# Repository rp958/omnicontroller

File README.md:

# OmniController

## Description

*OmniController* is an Open Hardware /  Open Source, all-in-one controller.

It was conceived with retrogaming solutions (such as emulators or FPGA) in mind but can accommodate to modern gaming as well. Its main goal is to cover original button layouts of most of the popular console controllers without having to remap buttons or use different controllers when playing games from different consoles libraries.

It uses the [**GP2040-CE**](https://gp2040-ce.info/) firmware which is well known for its [compatibility](https://gp2040-ce.info/usage#input-modes) with most modern and retro platforms as well as its [very low latency](https://gp2040-ce.info/#performance).

## Default keymap

Please note that the double L3 and R3 buttons (the ones on the joysticks and the face buttons ones) are wired in hardware. That means that if you chose, for exemple, to remap L3 to a different button, both L3s will be remapped to that button. This is due to the fact that all GPIOs available in the firmware/microcontroller are already in use. It is unlikely that you will need to use both joysticks and 6 faces buttons at the same time.

## Getting Started

### Prerequisites

Software:
- Firmware: [**GP2040-CE**](https://gp2040-ce.info/)
- (optional for modifying the PCB): [**KiCAD**](https://www.kicad.org/)
- (optional for modifying the case and buttons): [**FreeCAD**](https://www.freecad.org/)

Hardware:
- 4x M2x4x3.2 threaded inserts
- 4x M2x12 screws
- a soldering iron (to melt the inserts into the case, no actual soldering required)
- super glue
- USB-C cable
- a computer for installing the firmware

### Making the PCB

Download and extract the latest [*OmniController* release](https://github.com/rp958/omnicontroller/releases) file.

All the necessary files for PCB fabrication are located in *release/pcb/*.

Bill of materials:

| Item# | Designation                                                                                 | Manufacturer      | Part Number            | Package               | Value              | Quantity |
|-------|---------------------------------------------------------------------------------------------|-------------------|------------------------|-----------------------|--------------------|----------|
| 1     | UP1, DOWN1, LEFT1, RIGHT1, Credit1, Menu1, SEL1, START1, A1, B1, bC1, X1, Y2, Z1, BOOT_SEL1 | Omron Electronics | B3FS-1000P             |                       |                    | 15       |
| 2     | bR1, bR2, bL1, bL2                                                                          | Omron Electronics | B3F-3100               |                       |                    | 4        |
| 3     | C1, C2                                                                                      |                   |                        | 0805 (2012 Metric)    | 10u capacitor      | 2        |
| 4     | C10, C11                                                                                    |                   |                        | 0805 (2012 Metric)    | 1u capacitor       | 2        |
| 5     | C12, C13, C14, C3, C4, C5, C6, C7, C8, C9                                                   |                   |                        | 0805 (2012 Metric)    | 100n capacitor     | 10       |
| 6     | C15, C16                                                                                    |                   |                        | 0805 (2012 Metric)    | 15p capacitor      | 2        |
| 7     | LeftStick1, RightStick1                                                                     | Alps              | RKJXV122400R           | (THT)                 |                    | 2        |      
| 8     | J1                                                                                          | G-Switch          | GT-USB-7010ASV         |                       |                    | 1        |
| 9     | R1, R2                                                                                      |                   |                        | 0805 (2012 Metric)    | 27.4 ohms resistor | 2        |
| 10    | R3, R4                                                                                      |                   |                        | 0805 (2012 Metric)    | 1k resistor        | 2        |
| 11    | U1                                                                                          | Raspberry Pi      | RP2040                 | QFN-56 7×7mm          |                    | 1        |
| 12    | U2                                                                                          | Onsemi            | NCP1117ST33T3G         | SOT-223-3_TabPin2     |                    | 1        |
| 13    | U3                                                                                          | Winbond           | W25Q128JVSIM           | SOIC 208-mil          |                    | 1        |
| 14    | Y1                                                                                          | Abracon           | ABM8-272-T3            | Crystal SMD 3225 4Pin |                    | 1        |
| 15    | (Optionnal) J2                                                                              | GCT               | USB1046-GF-0190-L-B-B  | USB_A_Receptacle      |                    | 1        |

NOTE: J2 is only necessary for *Host USB* authentication mode. If not needed, can be left unpopulated.

NOTE: J3 is for development of and does not require populating.

### 3D Printing the case and buttons

You will need to print the following parts (all contained in *release/case/*).

Buttons:
- [ ] 1x dpad_bottom
- [ ] 1x dpad_top
- [ ] 2x joystick
- [ ] 2x button_select_start
- [ ] 2x button_cred_home
- [ ] 4x button_L_R
- [ ] 6x button_face 

Case:
- [ ] 1x case_back
- [ ] 1x case_front
- [ ] 1x middle_frame

For better printing results, it is recommended the following parts be sliced at an angle of 45 degrees and with supports:
- the joysticks
- case_top
- case_bottom

All the other parts should be printed flat and do not require any support.

Please note that depending on the quality and precision of your print, you might have to sand some parts.

### Assembling

1. Take the 2 parts of the D-Pad and glue them together back to back, making sure the two holes are aligned. 
2. Take the case front, melt the threaded inserts into the 4 holes using the soldering iron. 
3. Place all the face controls as well as L1 and R1 in their respective place. Make sure the rectangular holes in the back of the joysticks are placed horizontally. 
4. Place the PCB aligning the holes with the M2 inserts. Make sure the joystick axes go into the rectangular holes. 
5. Insert the middle frame. 
6. Place the L2 and R2 buttons. 
7. Close the controller using the back part, then screw it using the 4 M2 screws. Screw them firmly but not too tight. 
8. You're done!

### Flashing the firmware

1. Download the latest version of **GP2040-CE** from the project's [download page](https://gp2040-ce.info/downloads). You must use the link for the **Raspberry Pi Pico** microcontroller.
2. Unplug your controller.
3. Use a pin or an unfolded paperclip to press the reset button at the back of the controller. 
4. While pressing the reset button, plug the controller to your computer. Your computer should detect your controller as a mass storage device.
5. Copy the *.uf2* firmware file to the controller memory.
6. Once the file copy is finished, the controller should restart and be detected as an XInput (XBox360) controller by default.

Please refer to the [**GP2040-CE** installation documentation](https://gp2040-ce.info/installation) for more details.

### Recommended configuration

1. Unplug your controller.
2. Download the default [*omnicontroller_default.gp2040*](conf/omnicontroller_default.gp2040) configuration file on your computer.
3. Press and hold the S2 button. While still holding S2, plug the controller to your computer. Your computer should detect your controller as a network adapter.
4. Open the following URL in your Web Browser: [http://192.168.7.1](http://192.168.7.1). This should bring you to the *Web Configurator* interface.
5. Go to *Configuration* > *Data Backup and Restoration*.
6. Click on *Load* and select the *omnicontroller_default.gp2040* file you downloaded at step 2.
7. Click the *REBOOT* button, then *Controller*.

Please refer to the [**GP2040-CE** *Web Configurator* documentation](https://gp2040-ce.info/web-configurator/) for more details.

### Usage
 
Please refer to the [**GP2040-CE** usage documentation](https://gp2040-ce.info/usage)

### Troubleshooting

In case of problems, you can use **Hardware Tester's** [gamepad controller](https://hardwaretester.com/gamepad) in order to make sure you controller is detected correctly and that all buttons are functioning.

## Roadmap

- Several new features are considered, for instance adding an OLED screen, rumble, colord LEDs. Please join the discord via the project's [Patreon](https://www.patreon.com/omnicontroller) for discussing new features and/or new features prioritization.

## Known issues / Limitations

- At this stage, *Host USB* authentication mode for PS4/PS5 is implemented but has not been tester. Please read [*Additionnal PS4 settings*](https://gp2040-ce.info/web-configurator/menu-pages/settings/#additional-ps4-settings) from **GP2040-CE** *Settings* documentation. Any feedback is appreciated.

## License

Distributed under CERN-OHL-S version 2 or later. See [licence text](https://ohwr.org/cern_ohl_s_v2.txt) for more information.

## Contact

Please [e-mail me](mailto:omnicontroller@proton.me) if you want to contribute, especially if you have experience in electronics engineering, CAD or manufacturing.

## Attributions

OmniController uses several KiCAD component footprints and models from the [SnapEDA library](https://www.snapeda.com/parts/).

## Acknowledgments

Many thanks go to the [**GP2040-CE**](https://gp2040-ce.info/) development team.

## Help

If you want to help funding this project, any contribution is greatly welcome. This can help me acquire some prototyping equipment and spend more time on the development. To do so, please use my:

- [  Patreon](https://www.patreon.com/omnicontroller) page.
- [  Ko-fi](https://ko-fi.com/omnicontroller) page.

Thank you.

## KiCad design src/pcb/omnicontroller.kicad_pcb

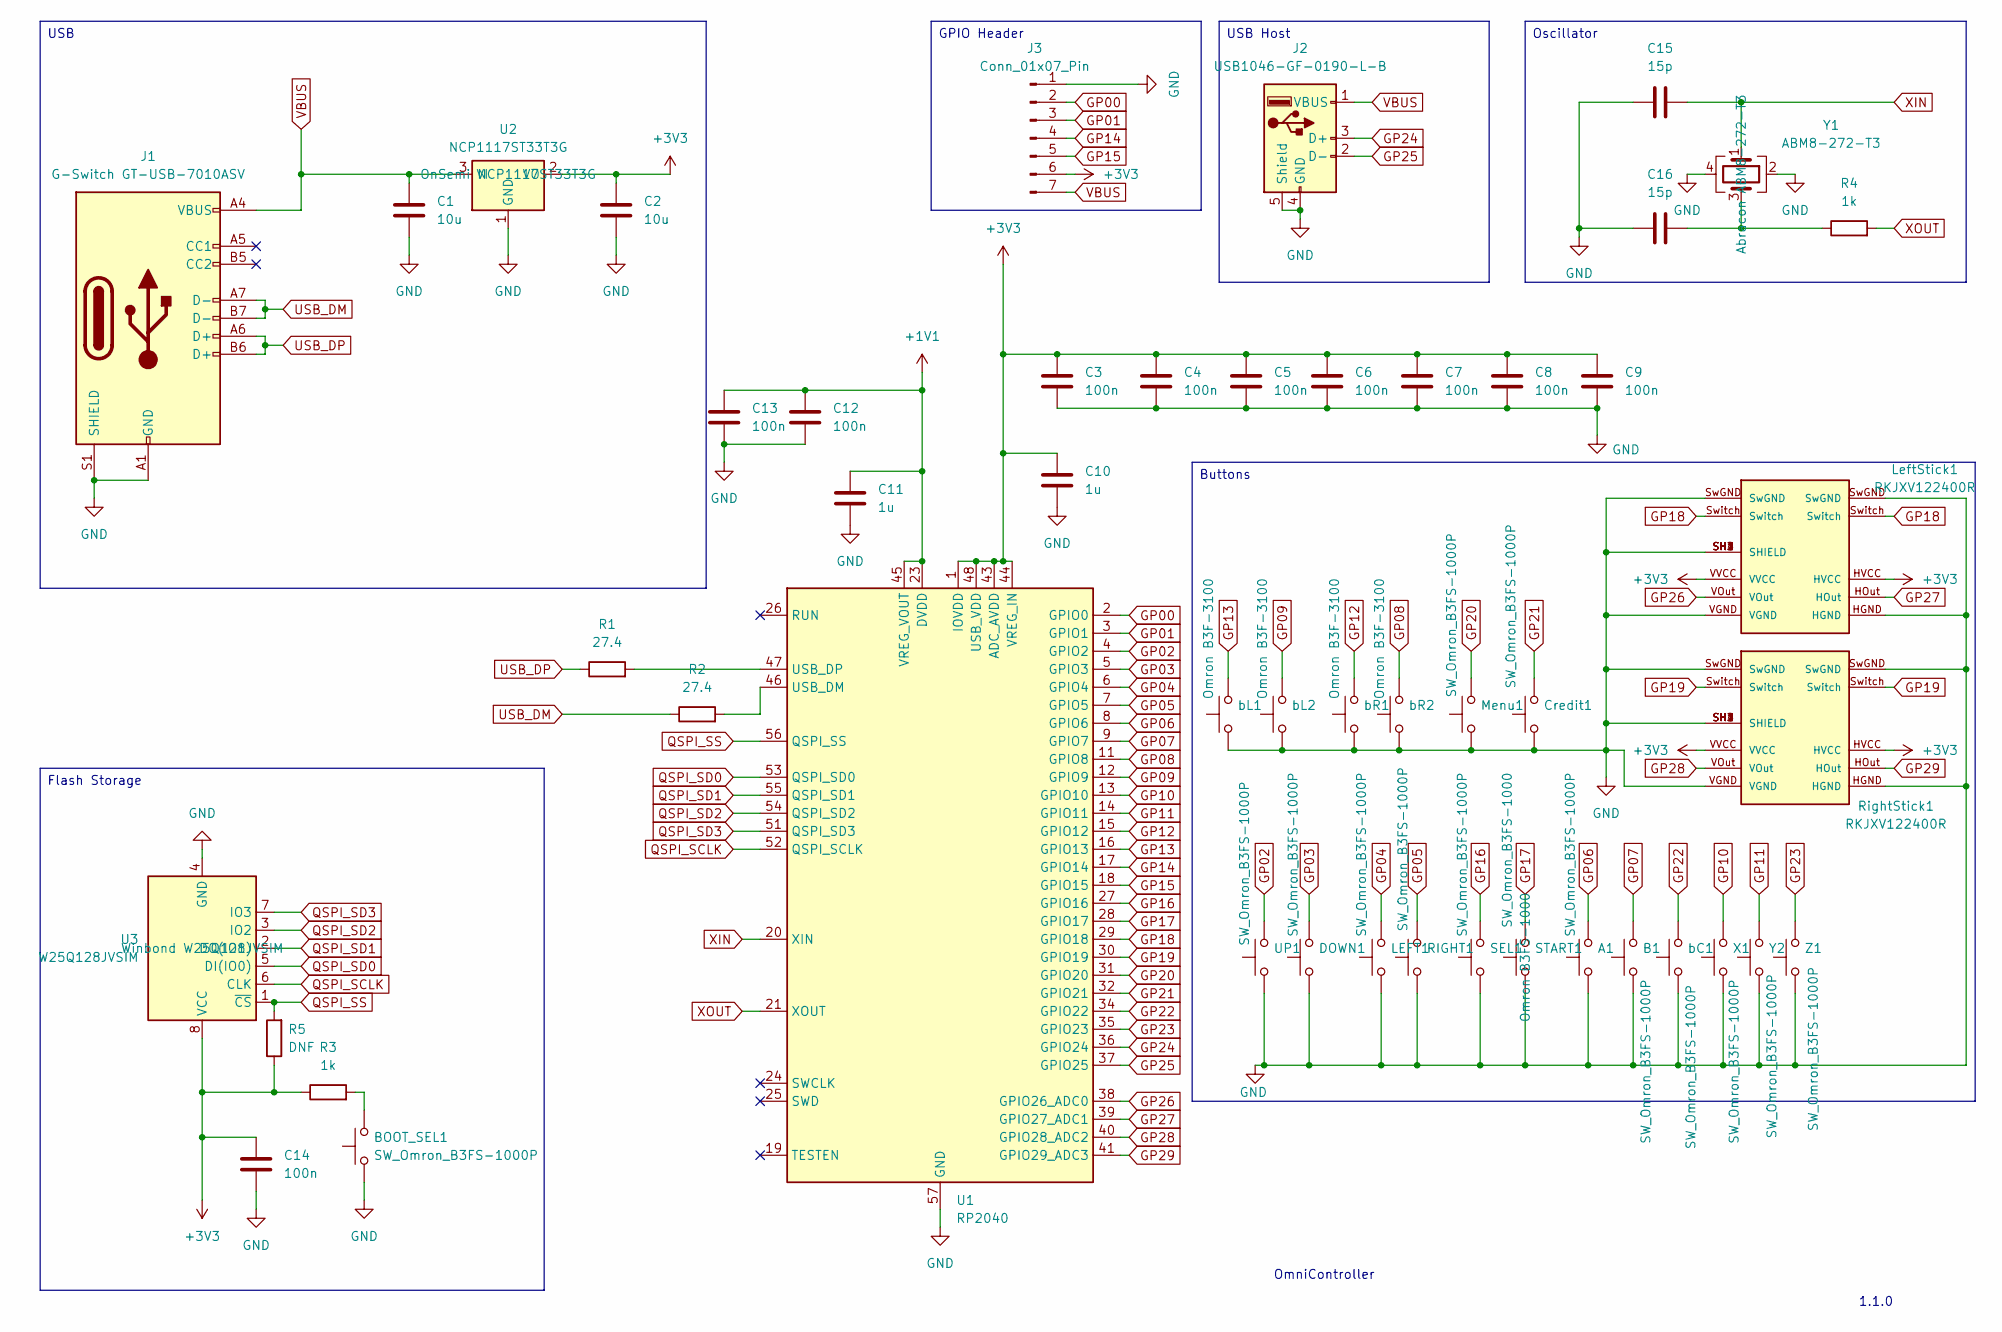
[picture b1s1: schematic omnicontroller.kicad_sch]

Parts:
A1: SW_Omron_B3FS-1000P; SW_SPST_Omron_B3FS-100xP
B1: SW_Omron_B3FS-1000P; SW_SPST_Omron_B3FS-100xP
BOOT_SEL1: SW_Omron_B3FS-1000P; SW_SPST_Omron_B3FS-100xP
C1, C2: 10u; C_0805_2012Metric
C3, C4, C5, C6, C7, C8, C9, C12, C13, C14: 100n; C_0805_2012Metric
C10, C11: 1u; C_0805_2012Metric
C15, C16: 15p; C_0805_2012Metric
Credit1: SW_Omron_B3FS-1000P; SW_SPST_Omron_B3FS-100xP
DOWN1: SW_Omron_B3FS-1000P; SW_SPST_Omron_B3FS-100xP
J1: G-Switch GT-USB-7010ASV; USB_C_Receptacle_G-Switch_GT-USB-7010ASV
J2: USB1046-GF-0190-L-B; USB_A_Receptacle_GCT_USB1046
J3: Conn_01x07_Pin; PinHeader_1x07_P2.54mm_Horizontal
LEFT1: SW_Omron_B3FS-1000P; SW_SPST_Omron_B3FS-100xP
LeftStick1: RKJXV122400R; SW_RKJXV122400R; PARTREV N/A
Menu1: SW_Omron_B3FS-1000P; SW_SPST_Omron_B3FS-100xP
R1, R2: 27.4; C_0805_2012Metric
R3, R4: 1k; C_0805_2012Metric
R5: DNF; C_0805_2012Metric
RIGHT1: SW_Omron_B3FS-1000P; SW_SPST_Omron_B3FS-100xP
RightStick1: RKJXV122400R; SW_RKJXV122400R; PARTREV N/A
SEL1: SW_Omron_B3FS-1000P; SW_SPST_Omron_B3FS-100xP
START1: SW_Omron_B3FS-1000; SW_SPST_Omron_B3FS-100xP
U1: RP2040; QFN-56-1EP_7x7mm_P0.4mm_EP3.2x3.2mm
U2: NCP1117ST33T3G; SOT-223-3_TabPin2
U3: W25Q128JVSIM; SOIC-8_5.3x5.3mm_P1.27mm
UP1: SW_Omron_B3FS-1000P; SW_SPST_Omron_B3FS-100xP
X1: SW_Omron_B3FS-1000P; SW_SPST_Omron_B3FS-100xP
Y1: ABM8-272-T3; Crystal_SMD_3225-4Pin_3.2x2.5mm
Y2: SW_Omron_B3FS-1000P; SW_SPST_Omron_B3FS-100xP
Z1: SW_Omron_B3FS-1000P; SW_SPST_Omron_B3FS-100xP
bC1: SW_Omron_B3FS-1000P; SW_SPST_Omron_B3FS-100xP
bL1, bL2: SW_B3F-3100
bR1, bR2: SW_B3F-3100

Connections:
+1V1: C11.1, C12.1, C13.1, U1.23 (DVDD), U1.45 (VREG_VOUT), U1.50 (DVDD)
GND: A1.1, B1.1, BOOT_SEL1.1, C1.2, C2.2, C3.2, C4.2, C5.2, C6.2, C7.2, C8.2, C9.2, C10.2, C11.2, C12.2, C13.2, C14.2, C15.1, C16.1, Credit1.1, DOWN1.1, J1.A1 (GND), J1.A12 (GND), J1.B1 (GND), J1.B12 (GND), J1.S1 (SHIELD), J2.4 (GND), J2.5 (Shield), J3.1, LEFT1.1, LeftStick1.HGND, LeftStick1.SH1 (SHIELD), LeftStick1.SH2 (SHIELD), LeftStick1.SH3 (SHIELD), LeftStick1.SH4 (SHIELD), LeftStick1.SwGND, LeftStick1.VGND, Menu1.1, RIGHT1.1, RightStick1.HGND, RightStick1.SH1 (SHIELD), RightStick1.SH2 (SHIELD), RightStick1.SH3 (SHIELD), RightStick1.SH4 (SHIELD), RightStick1.SwGND, RightStick1.VGND, SEL1.1, START1.1, U1.57 (GND), U2.1 (GND), U3.4 (GND), UP1.1, X1.1, Y1.2, Y1.4, Y2.1, Z1.1, bC1.1, bL1.1, bL2.1, bR1.1, bR2.1
GP00: J3.2, U1.2 (GPIO0)
GP01: J3.3, U1.3 (GPIO1)
GP02: U1.4 (GPIO2), UP1.2
GP03: DOWN1.2, U1.5 (GPIO3)
GP04: LEFT1.2, U1.6 (GPIO4)
GP05: RIGHT1.2, U1.7 (GPIO5)
GP06: A1.2, U1.8 (GPIO6)
GP07: B1.2, U1.9 (GPIO7)
GP08: U1.11 (GPIO8), bR2.2
GP09: U1.12 (GPIO9), bL2.2
GP10: U1.13 (GPIO10), X1.2
GP11: U1.14 (GPIO11), Y2.2
GP12: U1.15 (GPIO12), bR1.2
GP13: U1.16 (GPIO13), bL1.2
GP14: J3.4, U1.17 (GPIO14)
GP15: J3.5, U1.18 (GPIO15)
GP16: SEL1.2, U1.27 (GPIO16)
GP17: START1.2, U1.28 (GPIO17)
GP18: LeftStick1.Switch, U1.29 (GPIO18)
GP19: RightStick1.Switch, U1.30 (GPIO19)
GP20: Menu1.2, U1.31 (GPIO20)
GP21: Credit1.2, U1.32 (GPIO21)
GP22: U1.34 (GPIO22), bC1.2
GP23: U1.35 (GPIO23), Z1.2
GP24: J2.3 (D+), U1.36 (GPIO24)
GP25: J2.2 (D-), U1.37 (GPIO25)
GP26: LeftStick1.VOut, U1.38 (GPIO26_ADC0)
GP27: LeftStick1.HOut, U1.39 (GPIO27_ADC1)
GP28: RightStick1.VOut, U1.40 (GPIO28_ADC2)
GP29: RightStick1.HOut, U1.41 (GPIO29_ADC3)
unnamed: BOOT_SEL1.2, R3.2
unnamed: C16.2, R4.1, Y1.3
unnamed: R2.2, U1.46 (USB_DM)
unnamed: R1.2, U1.47 (USB_DP)
QSPI_SCLK: U1.52 (QSPI_SCLK), U3.6 (CLK)
QSPI_SD0: U1.53 (QSPI_SD0), U3.5 (DI(IO0))
QSPI_SD1: U1.55 (QSPI_SD1), U3.2 (DO(IO1))
QSPI_SD2: U1.54 (QSPI_SD2), U3.3 (IO2)
QSPI_SD3: U1.51 (QSPI_SD3), U3.7 (IO3)
USB_DM: J1.A7 (D-), J1.B7 (D-), R2.1
USB_DP: J1.A6 (D+), J1.B6 (D+), R1.1
VBUS: C1.1, J1.A4 (VBUS), J1.A9 (VBUS), J1.B4 (VBUS), J1.B9 (VBUS), J2.1 (VBUS), J3.7, U2.3 (VI)
XIN: C15.2, U1.20 (XIN), Y1.1
XOUT: R4.2, U1.21 (XOUT)

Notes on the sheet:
1.1.0
OmniController
Flash Storage
Buttons
USB
USB Host
Oscillator
GPIO Header

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
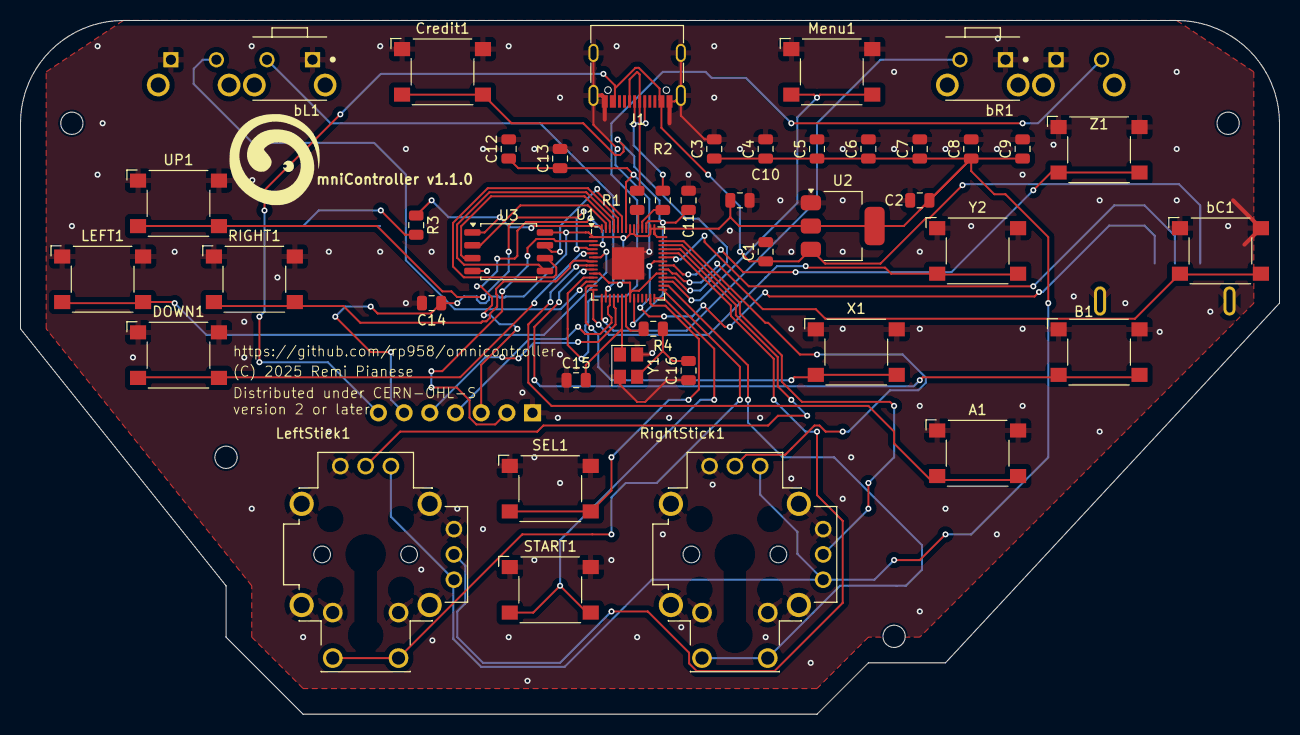
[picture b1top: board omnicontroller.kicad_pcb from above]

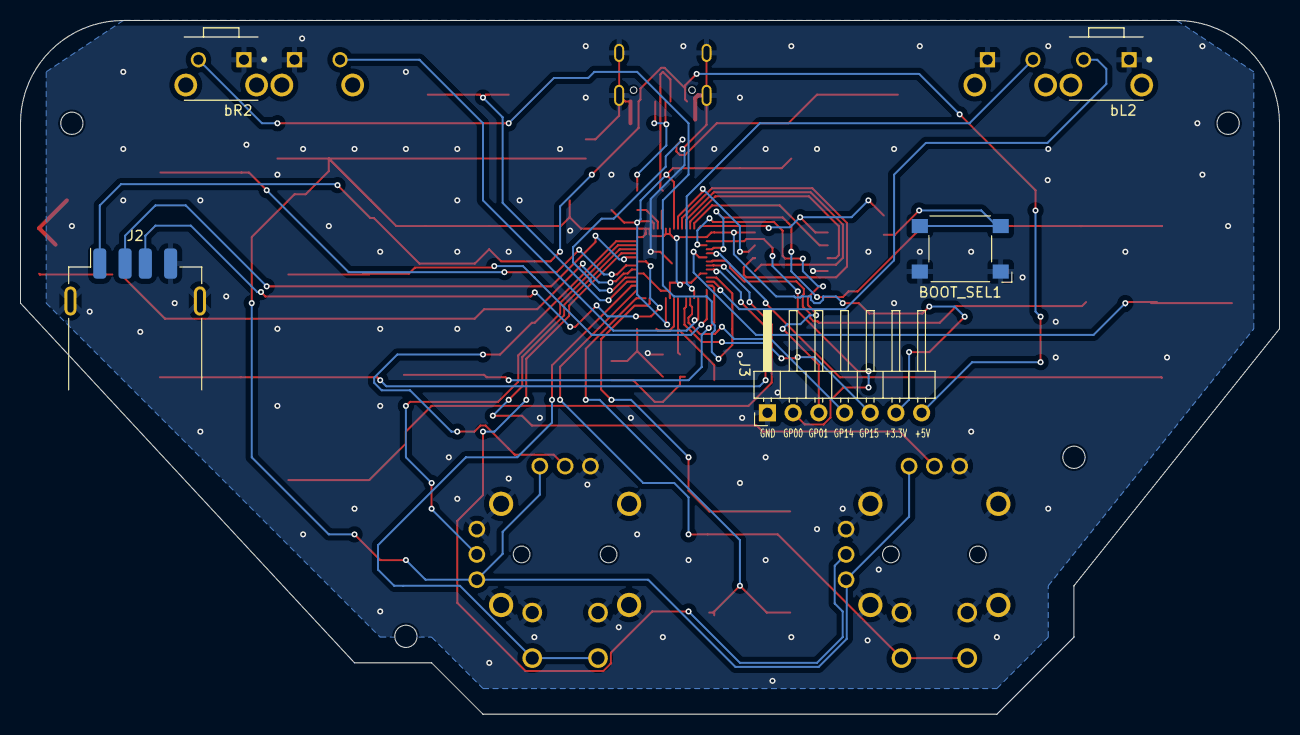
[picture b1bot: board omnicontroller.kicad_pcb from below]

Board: 2 copper layers, 124.5 x 68.6 mm, 48 parts (5 on the bottom side), 48 nets.

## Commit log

2025-03-13 change name
2025-03-13 add default conf
2025-03-13 add pcb
2025-03-13 add readme
2025-03-14 Fix typos
2025-03-14 Add CHANGES.txt
2025-03-14 Add freecad project with case and buttons
2025-03-18 Add funding details
2025-03-18 change to white patreon logo
2025-03-18 convert to kicad 9.0 file format
2025-03-18 add RKJXV122400 footprint
2025-03-18 fix some drc warnings
2025-03-18 add release files
2025-03-19 update instructions to match release files
2025-03-21 move L1,L2, R1 and R2 buttons to top side
    replace B3FS-1000 with B3F-3100 for those buttons
2025-03-21 add omron B3F-3100 footprint
2025-03-21 connect buttons C and Z to GPIO 22 and 23
2025-03-21 add USB A port for PS4/5 host mode authentication
2025-03-22 add pinheader with all unused GPIO
2025-03-22 Add 3d models to pcb
2025-03-25 update usb A connector
2025-03-25 update pcb release files
2025-03-25 import v1.1.0 of pcb + adjust dpad button alignment
2025-03-25 add pcb mesh file
2025-03-25 modify case to fit GPIO pin connector and host USB connectore
2025-03-25 move L1,L2, R1 and R2 buttons on top side (printable case and buttons)
2025-03-25 update case and buttons release files
2025-03-27 fix L1/R1 stops go through front
2025-03-27 update front release file
2025-04-25 Adjust shoulder buttons size
2025-04-25 Update default config
2025-04-25 Update release file
2025-04-30 Add missing component footprints and 3D models

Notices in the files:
src/pcb/omnicontroller.kicad_pcb:
(C) 2025 Remi Pianese
